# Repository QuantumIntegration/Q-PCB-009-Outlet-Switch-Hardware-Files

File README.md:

# Quantum DIY Kit Hardware Files - Outlet Switch
## Introduction

This repository contains all the hardware files necessary to build the PCBs and assemble the DIY kits. The PCBs can be ordered from for example [JLCPCB](https://jlcpcb.com/) or [PCBWay](https://www.pcbway.com/). The components can be sourced mostly from [Amazon](https://amazon.com/) or [Digikey](https://digikey.com/), according to the links in the BOM file.

## Download the correct revision

If you are nor familiar with the git version control system, please follow these simple steps to download your version of the DIY kit

<em>1. Click the branch button</em>

<em>2. Select the branch matching your revision</em>

<em>3. Click the Code button</em>

<em>4. Download the ZIP and extract it on your machine</em>

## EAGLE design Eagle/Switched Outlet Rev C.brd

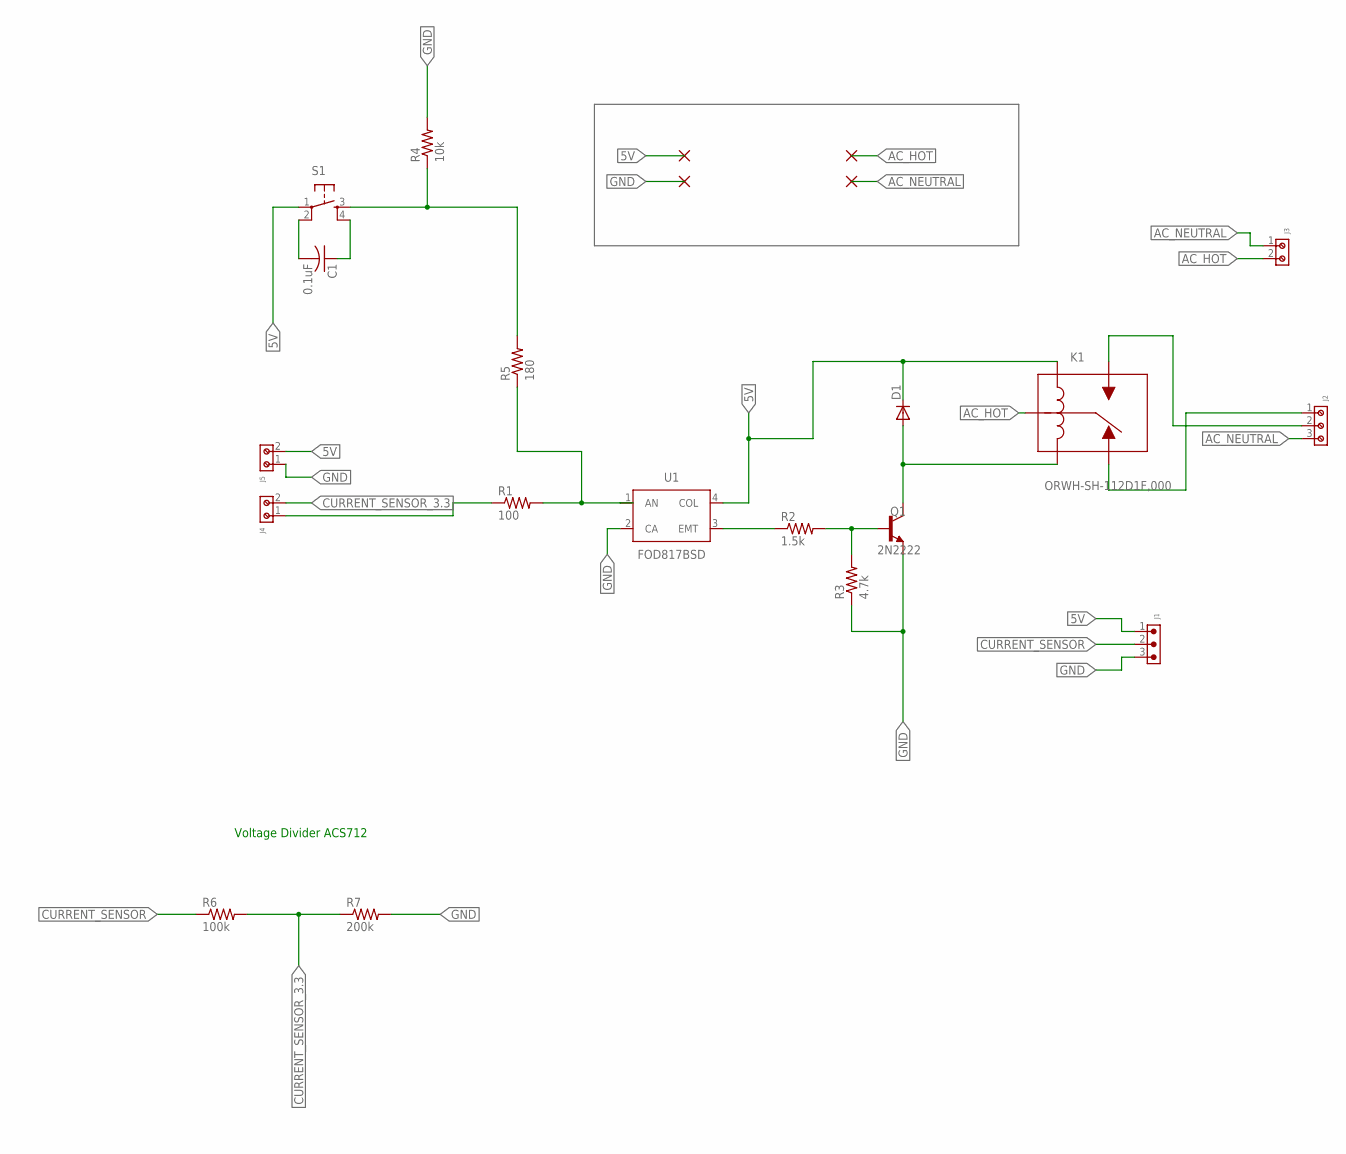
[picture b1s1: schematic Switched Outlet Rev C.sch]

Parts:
C1: 0.1uF; C050-024X044
D1: 1N4000; DO41-10
J1: 6130XX11121_61300311121; 61300311121
J2: 691102710003
J3: 691102710002
J4, J5: 691103110002
K1: ORWH-SH-112D1F,000
Q1: 2N2222; TO92-EBC-OVAL
R1: 100; 0207/10
R2: 1.5k; 0207/10
R3: 4.7k; 0207/10
R4: 10k; 0207/10
R5: 180; 0207/10
R6: 100k; 0207/10
R7: 200k; 0207/10
S1: TACTILE-BUTTON10XX; B3F-10XX
U1: FOD817BSD; DIP1016W60P279L460H460Q4B

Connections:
5V: D1.C, J1.1, J5.2, K1.1, S1.1, U1.4 (COL)
AC_HOT: J3.2, K1.2
AC_NEUTRAL: J2.3, J3.1
CURRENT_SENSOR: J1.2, R6.1
CURRENT_SENSOR_3.3: J4.2, R6.2, R7.1
GND: J1.3, J5.1, Q1.E, R3.1, R4.2, R7.2, U1.2 (CA)
unnamed: J4.1, R1.1
unnamed: R1.2, R5.1, U1.1 (AN)
unnamed: R2.1, U1.3 (EMT)
unnamed: Q1.B, R2.2, R3.2
unnamed: D1.A, K1.3, Q1.C
unnamed: J2.1, K1.4
unnamed: J2.2, K1.5
unnamed: R4.1, R5.2, S1.3 (S)
unnamed: C1.2, S1.2 (P1)
unnamed: C1.1, S1.4 (S1)

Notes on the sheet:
Voltage Divider ACS712

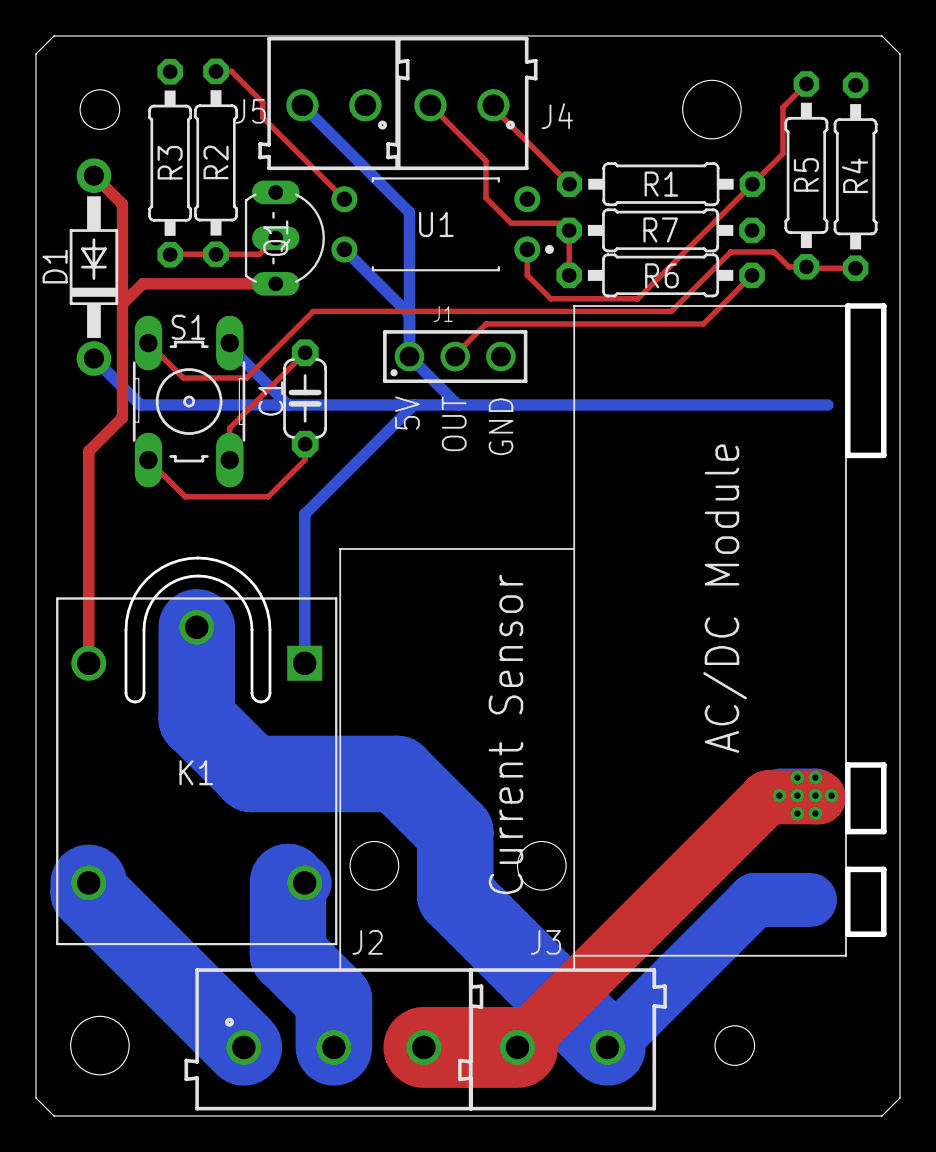
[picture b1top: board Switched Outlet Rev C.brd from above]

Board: 2 copper layers, 47.7 x 59.7 mm, 18 parts (0 on the bottom side), 16 nets.

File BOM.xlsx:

Index | Part | Value | Quantitiy | Designators | Package | Comments | Specific Part Reference | Part Link Example
1 | Resistor | 100 | 1 | R1 | 0207/10 | 1/4 W |  | https://www.amazon.com/SIQUK-Resistors-Resistor-Assortment-E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
2 | Resistor | 1.5k | 1 | R2 | 0207/10 | 1/4 W |  | https://www.amazon.com/SIQUK-Resistors-Resistor-Assortment-E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
3 | Resistor | 4.7k | 1 | R3 | 0207/10 | 1/4 W |  | https://www.amazon.com/SIQUK-Resistors-Resistor-Assortment-E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
4 | Resistor | 10k | 1 | R4 | 0207/10 | 1/4 W |  | https://www.amazon.com/SIQUK-Resistors-Resistor-Assortment-E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
5 | Resistor | 180 | 1 | R5 | 0207/10 | 1/4 W |  | https://www.amazon.com/SIQUK-Resistors-Resistor-Assortment-E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
6 | Resistor | 100k | 1 | R6 | 0207/10 | 1/4 W |  | https://www.amazon.com/SIQUK-Resistors-Resistor-Assortment-E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
7 | Resistor | 200k | 1 | R7 | 0207/10 | 1/4 W |  | https://www.amazon.com/SIQUK-Resistors-Resistor-Assortment-E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
8 | Diode | 1N4001 | 1 | D1 |  |  |  | https://www.digikey.com/product-detail/en/comchip-technology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
9 | Ceramic Capacitor | 100n | 1 | C1 | 024x044 |  |  | https://www.digikey.com/product-detail/en/kemet/C315C104M5U5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
10 | Tactile Button |  | 1 | S1 | B3F-10xx |  | Omron B3F-1020 | https://www.digikey.com/en/products/detail/omron-electronics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
11 | Terminal |  | 1 | J3 |  | 5.0mm, 1x2 |  | https://www.digikey.com/en/products/detail/w%C3%BCrth-elektr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
12 | Terminal |  | 1 | J2 |  | 5.0mm, 1x3 |  | https://www.digikey.com/en/products/detail/w%C3%BCrth-elektr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
13 | Terminal |  | 2 | J4, J5 |  | 3.50mm, 1x2 |  | https://www.digikey.com/product-detail/en/w%C3%BCrth-elektro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
14 | Header |  | 1 | J1 | 0.1 | 1x2, male |  | https://www.amazon.com/MCIGICM-Header-2-45mm-Arduino-Connect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
15 | Transistor PNP |  | 1 | Q1 | TO-92 |  | 2N2222 | https://www.amazon.com/Pieces-2N2222-Transistor-Through-2N22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
16 | Relay |  | 1 | K1 |  |  |  | https://www.amazon.com/Senmod-Household-Appliance-SRD-05VDC-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
17 | Optocoupler |  | 1 | U1 | DIP-4 |  |  | https://www.amazon.com/BOJACK-PC817-OPTOCOUPLER-Installation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
18 | M2 Standoff |  | 2 |  |  | 15mm, Female-Female |  | https://www.amazon.com/gp/product/B07CNF3W7B/ref=ppx_yo_dt_b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
19 | M2 Standoff |  | 2 |  |  | 20mm, Male-Female |  | https://www.amazon.com/gp/product/B07CNF3W7B/ref=ppx_yo_dt_b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
20 | M2 Screw |  | 4 |  |  | 5mm |  | https://www.amazon.com/gp/product/B07CNF3W7B/ref=ppx_yo_dt_b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
21 | M3 Screw |  | 2 |  |  | 6mm |  | https://www.amazon.com/gp/product/B07CNF3W7B/ref=ppx_yo_dt_b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
22 | M2 Standoff Plastic |  | 2 |  |  | 15mm, Female-Female PLASTIC! |  | https://www.amazon.com/gp/product/B07CNF3W7B/ref=ppx_yo_dt_b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
23 | M2 Screw Plastic |  | 4 |  |  | 5mm PLASTIC! |  | https://www.amazon.com/gp/product/B07CNF3W7B/ref=ppx_yo_dt_b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
24 | Power Meter |  | 1 |  |  | with M2 mounting holes | ACS712 Board | https://www.amazon.com/SUBALIGU-Current-Detector-ACS712ELC-A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
25 | Power Supply |  | 1 |  |  |  | RPD10W1S | https://www.amazon.com/Converter-Universal-Isolated-Switchin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

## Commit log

2021-07-12 iniital commit
2021-07-12 initial content
2021-12-17 added schematic
2022-01-19 added Arduino files

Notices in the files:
parts and their libraries:
Wurth_Connectors_WR-TBL Wire Protector: Copyright: Würth Elektronik
